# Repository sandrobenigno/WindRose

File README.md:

# The WindRose Project
Custom Hardware , Firmware and Software for Robotic Cellular Automata Experiments.

### We’re used to hearing about evolution by competition, but what about thinking about things that evolve from cooperation?
<p>We can learn a lot about ourselves by simulating robotic beings communicating, sharing information, tools and interacting as a community of living beings. In these simulations, questions emerge such as the importance of synchronicity between beings, the need for a shared language for mutual understanding, among many other issues. That’s what this project and research is about.</p>

<p>Author: Sandro Benigno, due to the inspiration and all the applied resources from fellow professor Marilia Lyra Bergamo. She is the one who made this project possible and guided me with her research on Robotic Plants and Complexity Theories.</p>

### The Wiki Pages

<p>In the <a href="https://github.com/sandrobenigno/WindRose/wiki">wiki pages</a> you can learn about the board, including the pinout and its usage.</p>

### Code documentation
All the files and classes are <a target="_blank" rel="noopener noreferrer" href="https://sandrobenigno.github.io/WindRose/html/index.html">documented here</a>.

### Fabrication

<p>We fabricate the boards through Seeed Fusion PCB Assembly Service. Check how to <a href="https://github.com/sandrobenigno/WindRose/wiki/Fabricate-yours%21">fabricate yours!</a></p>

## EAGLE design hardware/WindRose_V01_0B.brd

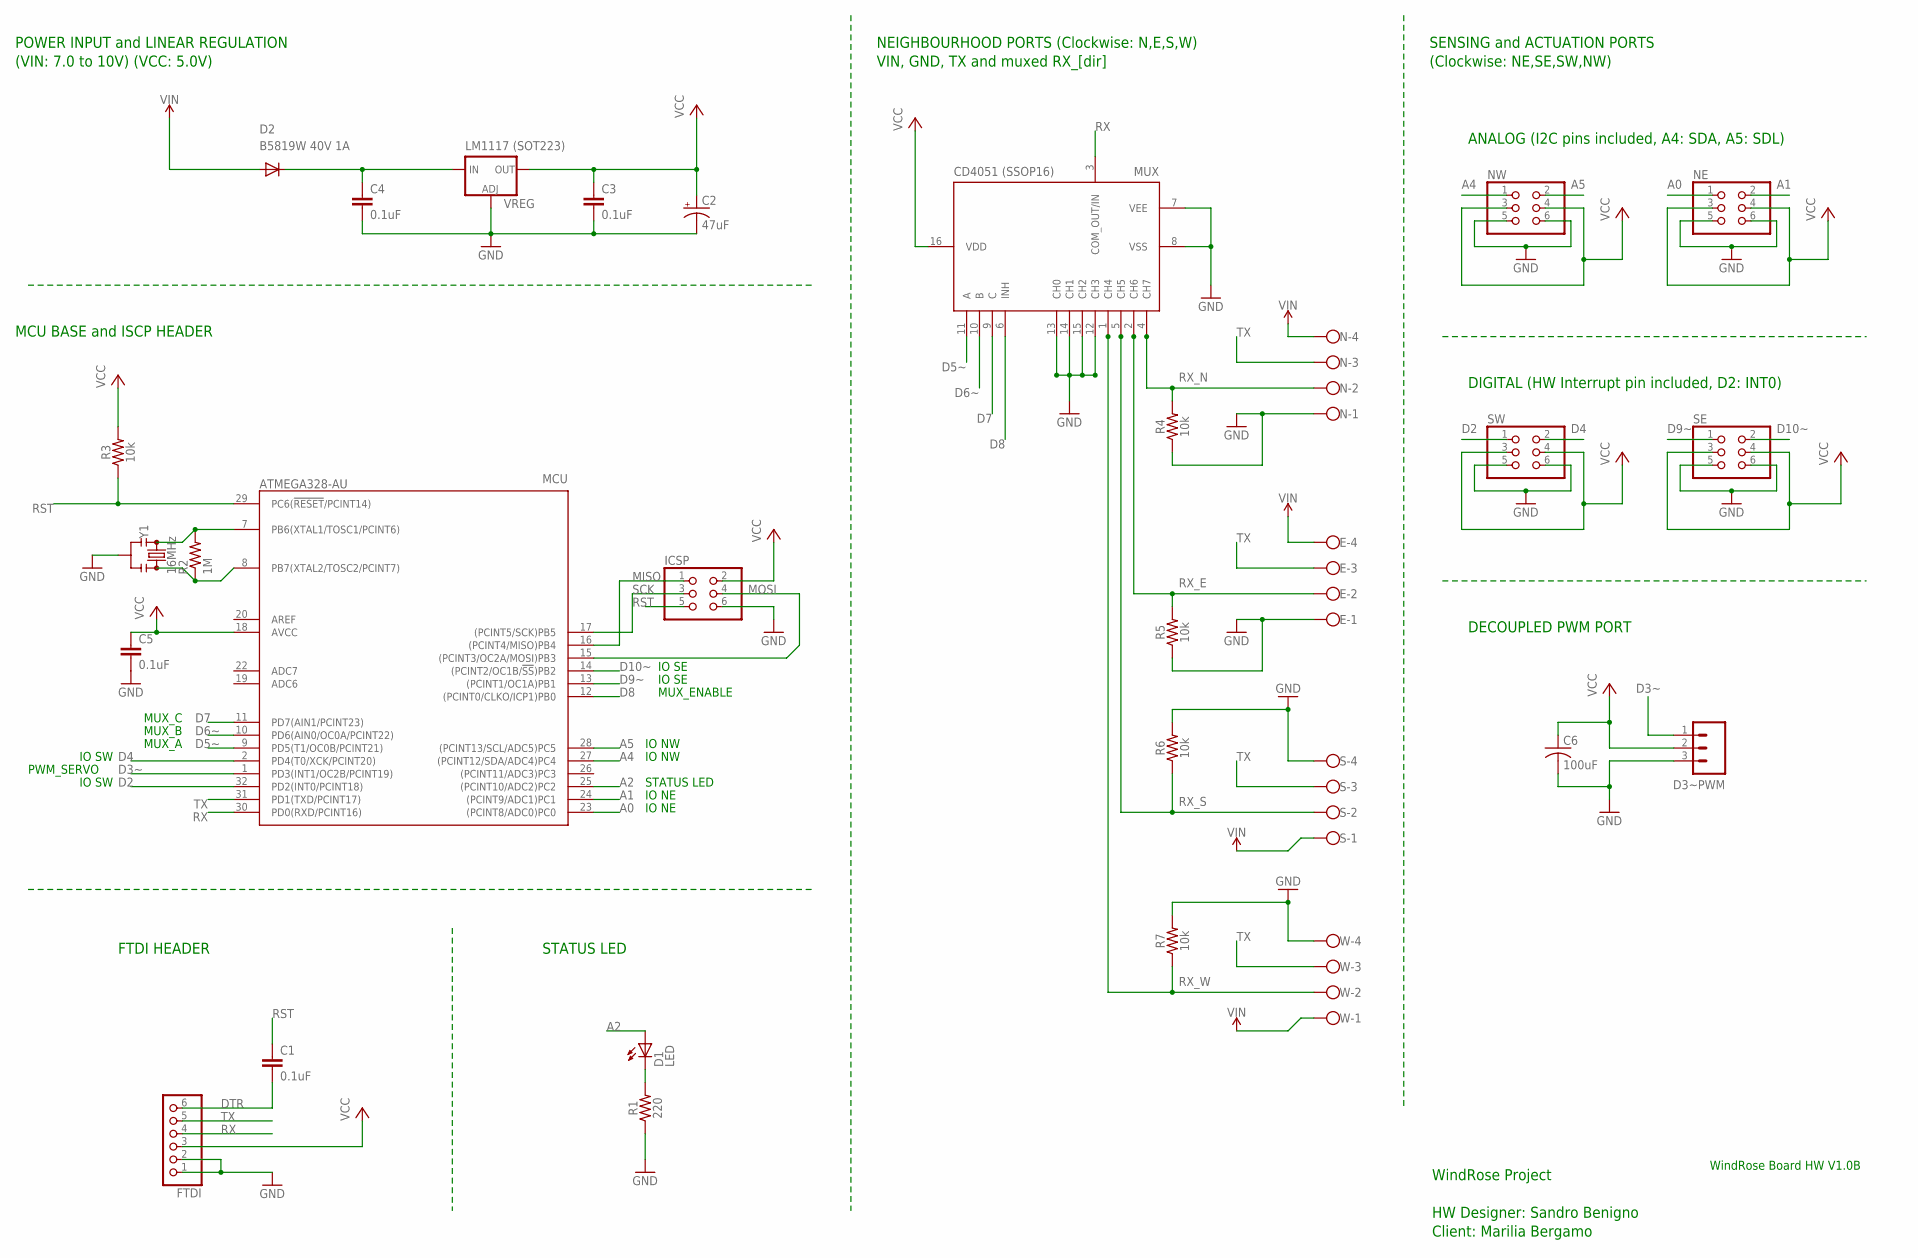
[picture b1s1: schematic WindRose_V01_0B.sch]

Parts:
C1, C3, C4, C5: 0.1uF; 0402
C2: 47uF; EIA3216
C6: 100uF; C3216
D1: LED; CHIP-LED0805
D2: B5819W 40V 1A; SOD123
D3~PWM: 455-1750-1-ND; 1X03
E: W237-4
FTDI: PINHD-1X6B; 1X06-BIG
ICSP: PINHD-2X3; 2X03
MCU: ATMEGA328-AU; QFP32_7X7_0.80
MUX: CD4051SSOP16; SSOP16
N: W237-4
NE: PINHD-2X3; 2X03
NW: PINHD-2X3; 2X03
R1: 220; 0603
R2: 1M; R0402
R3, R4, R5, R6, R7: 10k; 0402
S: W237-4
SE: PINHD-2X3; 2X03
SW: PINHD-2X3; 2X03
VREG: V_REG_LM1117SOT223; SOT223
W: W237-4
Y1: 16MHz; RESONATOR-SMD-3.2X1.3

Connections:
A0: MCU.23 ((PCINT8/ADC0)PC0), NE.1
A1: MCU.24 ((PCINT9/ADC1)PC1), NE.2
A2: D1.A, MCU.25 ((PCINT10/ADC2)PC2)
A4: MCU.27 ((PCINT12/SDA/ADC4)PC4), NW.1
A5: MCU.28 ((PCINT13/SCL/ADC5)PC5), NW.2
D2: MCU.32 (PD2(INT0/PCINT18)), SW.1
D3~: D3~PWM.1, MCU.1 (PD3(INT1/OC2B/PCINT19))
D4: MCU.2 (PD4(T0/XCK/PCINT20)), SW.2
D5~: MCU.9 (PD5(T1/OC0B/PCINT21)), MUX.11 (A)
D6~: MCU.10 (PD6(AIN0/OC0A/PCINT22)), MUX.10 (B)
D7: MCU.11 (PD7(AIN1/PCINT23)), MUX.9 (C)
D8: MCU.12 ((PCINT0/CLKO/ICP1)PB0), MUX.6 (INH)
D9~: MCU.13 ((PCINT1/OC1A)PB1), SE.1
D10~: MCU.14 ((PCINT2/OC1B/!SS!)PB2), SE.2
DTR: C1.2, FTDI.6
GND: C2.-, C3.2, C4.2, C5.2, C6.2, D3~PWM.3, E.1, FTDI.1, FTDI.2, ICSP.6, MCU.3 (GND), MCU.5 (GND), MCU.21 (GND), MUX.7 (VEE), MUX.8 (VSS), MUX.12 (CH3), MUX.13 (CH0), MUX.14 (CH1), MUX.15 (CH2), N.1, NE.5, NE.6, NW.5, NW.6, R1.1, R4.1, R5.1, R6.2, R7.2, S.4, SE.5, SE.6, SW.5, SW.6, VREG.1 (ADJ), W.4, Y1.2
MISO: ICSP.1, MCU.16 ((PCINT4/MISO)PB4)
MOSI: ICSP.4, MCU.15 ((PCINT3/OC2A/MOSI)PB3)
unnamed: MCU.8 (PB7(XTAL2/TOSC2/PCINT7)), R2.1, Y1.3
unnamed: MCU.7 (PB6(XTAL1/TOSC1/PCINT6)), R2.2, Y1.1
unnamed: D1.C, R1.2
unnamed: C4.1, D2.C, VREG.3 (IN)
RST: C1.1, ICSP.5, MCU.29 (PC6(!RESET!/PCINT14)), R3.1
RX: FTDI.4, MCU.30 (PD0(RXD/PCINT16)), MUX.3 (COM_OUT/IN)
RX_E: E.2, MUX.2 (CH6), R5.2
RX_N: MUX.4 (CH7), N.2, R4.2
RX_S: MUX.5 (CH5), R6.1, S.2
RX_W: MUX.1 (CH4), R7.1, W.2
SCK: ICSP.3, MCU.17 ((PCINT5/SCK)PB5)
TX: E.3, FTDI.5, MCU.31 (PD1(TXD/PCINT17)), N.3, S.3, W.3
VCC: C2.+, C3.1, C5.1, C6.1, D3~PWM.2, FTDI.3, ICSP.2, MCU.4 (VCC), MCU.6 (VCC), MCU.18 (AVCC), MUX.16 (VDD), NE.3, NE.4, NW.3, NW.4, R3.2, SE.3, SE.4, SW.3, SW.4, VREG.2 (OUT), VREG.4 (OUT)
VIN: D2.A, E.4, N.4, S.1, W.1

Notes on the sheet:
PWM_SERVO
MUX_A
MUX_B
MUX_C
IO SW
IO NE
IO NW
IO SE
MUX_ENABLE
STATUS LED
POWER INPUT and LINEAR REGULATION (VIN: 7.0 to 10V) (VCC: 5.0V)
NEIGHBOURHOOD PORTS (Clockwise: N,E,S,W) VIN, GND, TX and muxed RX_[dir]
SENSING and ACTUATION PORTS (Clockwise: NE,SE,SW,NW)
FTDI HEADER
MCU BASE and ISCP HEADER
DECOUPLED PWM PORT
WindRose Project HW Designer: Sandro Benigno Client: Marilia Bergamo
WindRose Board HW V1.0B
ANALOG (I2C pins included, A4: SDA, A5: SDL)
DIGITAL (HW Interrupt pin included, D2: INT0)
CD4051 (SSOP16)
LM1117 (SOT223)
MUX

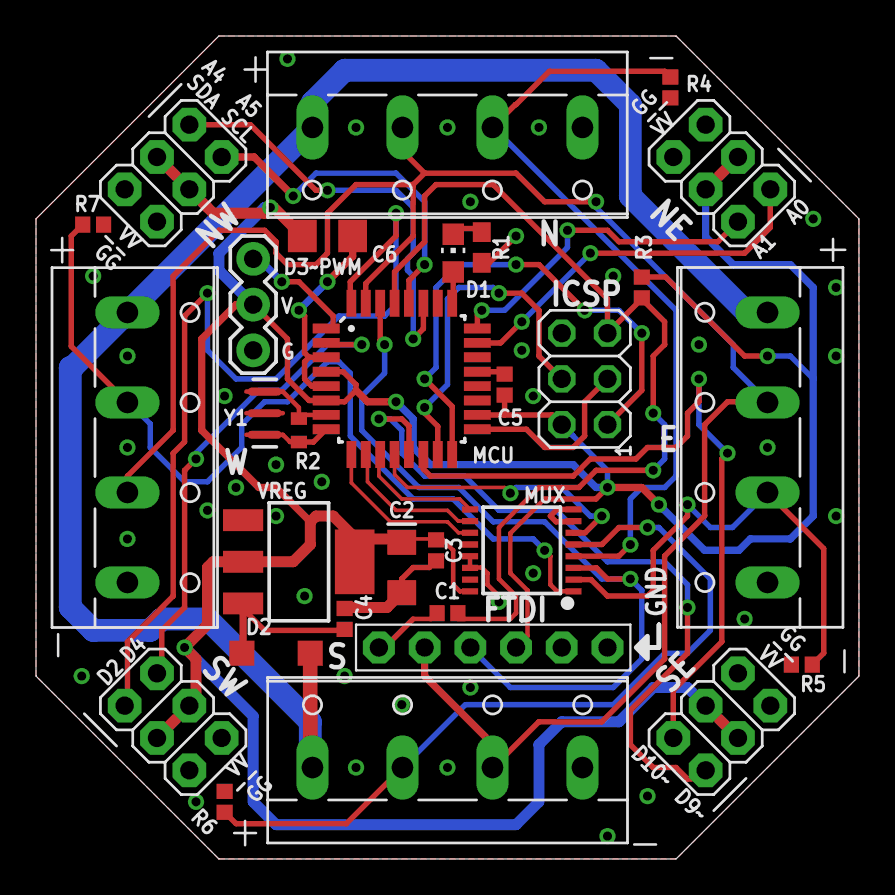
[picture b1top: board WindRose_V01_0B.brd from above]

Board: 2 copper layers, 45.7 x 45.7 mm, 31 parts (1 on the bottom side), 32 nets.

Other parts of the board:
U$1: WINDROSE_LOGO

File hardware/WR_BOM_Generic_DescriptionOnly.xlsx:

Part | Value | Device | Package
C1 | 0.1uF | 0.1UF-0402-6.3V-10%-X7R | 0402
C2 | 47uF | 10UF-POLAR-EIA3216-16V-10%(TANT) | EIA3216
C3 | 0.1uF | 0.1UF-0402-6.3V-10%-X7R | 0402
C4 | 0.1uF | 0.1UF-0402-6.3V-10%-X7R | 0402
C5 | 0.1uF | 0.1UF-0402-6.3V-10%-X7R | 0402
C6 | 100uF | C-USC3216 | 3216
D1 | LED | LEDCHIP-LED0805 | 0805
D2 | SS24FL | DIODE-SOD123 | SOD123
MCU | ATMEGA328-AU | ATMEGA328-AU | QFP32_7X7_0.80
MUX | CD4051SSOP16 | CD4051SSOP16 | SSOP16
R1 | 220 | 220OHM-0603-1/10W-1% | 0603
R2 | 1M | R-US_R0402 | 0402
R3 | 10k | 10KOHM-0402-1/16W-1% | 0402
R4 | 10k | 10KOHM-0402-1/16W-1% | 0402
R5 | 10k | 10KOHM-0402-1/16W-1% | 0402
R6 | 10k | 10KOHM-0402-1/16W-1% | 0402
R7 | 10k | 10KOHM-0402-1/16W-1% | 0402
VREG |  | V_REG_AMS1117-5.0_SOT223 | SOT223
Y1 | 16MHz | RESONATOR-16MHZSMD_3.2X1.3 | RESONATOR-SMD-3.2X1.3

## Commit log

2021-12-10 Adding doc folder with an image
2021-12-11 Implementing Lifetime, Debug directives and a GUI for Telemetry
2021-12-11 Fixing hardcoded directives and config issues
2021-12-11 Fixing comments and the maximum DATA_buffer size
2021-12-13 Implementing the Naighbourhood State Mapping
2021-12-13 Implementing the Neighbourhood State Mapping
2021-12-14 Improved Serial Buffering Strategy
2021-12-15 Updated WindRose Monitor for Linux
2021-12-16 New features implemented on WindRose Monitor GUI
2021-12-17 Diagonal neighbor inference implemented
2021-12-17 Fixing typos
2021-12-17 Improving Neighbor Tracking
2021-12-19 Fine tuning the synchronism
2021-12-21 Code and GUI Optimizations
2021-12-21 Removing duplicated GUI auto generated source
2021-12-21 Updated GUI files Jar and Java
2021-12-22 Cleaning debug code
2021-12-31 Create Licence.md
    Adding the licence Creative Commons By SA 4.0
2021-12-31 Bug fixing and updates
2021-12-31 Adding doxygen header
2021-12-31 Creating docs folder
2022-01-03 Doxygen comments added
2022-01-03 Creating a DoxyFile and the docs folder
2022-01-03 Create main.yml
    Action to automate Doxygen documentation.
2022-01-03 Auto commit
2022-01-03 Improving some Doxygen comments
2022-01-03 Fixing AutoComit Issues
2022-01-03 Update Doxyfile
2022-01-03 Update images folder
2022-01-03 Update Doxygen documentation
2022-01-03 Update Doxygen documentation and class names
2022-01-04 Explicit enumeration indexing
2022-01-06 Update class Being and Doxygen comments
2022-01-06 Fixing typo
2022-01-06 Update comments
2022-01-08 Updated image
2022-01-08 New front image
2022-01-08 Fixing a typo
2022-01-08 Pre-release update
2022-01-20 TEMPLATE_RELATIONS added to Doxygen
2022-01-20 CALL_GRAPH added to Doxygen
2022-02-12 Changin names of constants conflicting with AVR toolchain names
2022-02-12 Change of constants conflicting with AVR toolchain ones
2022-02-12 Some extra comments added
2022-08-16 LED set as off on setup block and few comments added
2023-03-27 Including the bootloader
2023-06-01 Adding the hardware files
2023-06-16 Update README.md
    Added DOI badge from Zenodo.
2024-03-27 Updated bootloader for Atmega328P
2024-06-09 Cicardian class implemented
2024-06-09 Update main.yml
    Changing from actions/checkout@v2 to actions/checkout@v3
2024-07-08 Updated bootloader
2024-08-12 Updated BOM and added a generic, more descriptive version
2026-06-10 Zenodo badge fixing
2026-06-10 Fix DOI badge link in README.md
    Updated DOI badge image link in README.

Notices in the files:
parts and their libraries:
MyLib_SAN: Licensing: Creative Commons ShareAlike 4.0 International - https://creativecommons.org/licenses/by-sa/4.0
